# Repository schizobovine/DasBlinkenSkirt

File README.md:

# DasBlinkenSkirt
Firmware, hardware (?), and potentially sewing patterns for a RGB, motion-reactive, fiber-optic skirt (of a sort).

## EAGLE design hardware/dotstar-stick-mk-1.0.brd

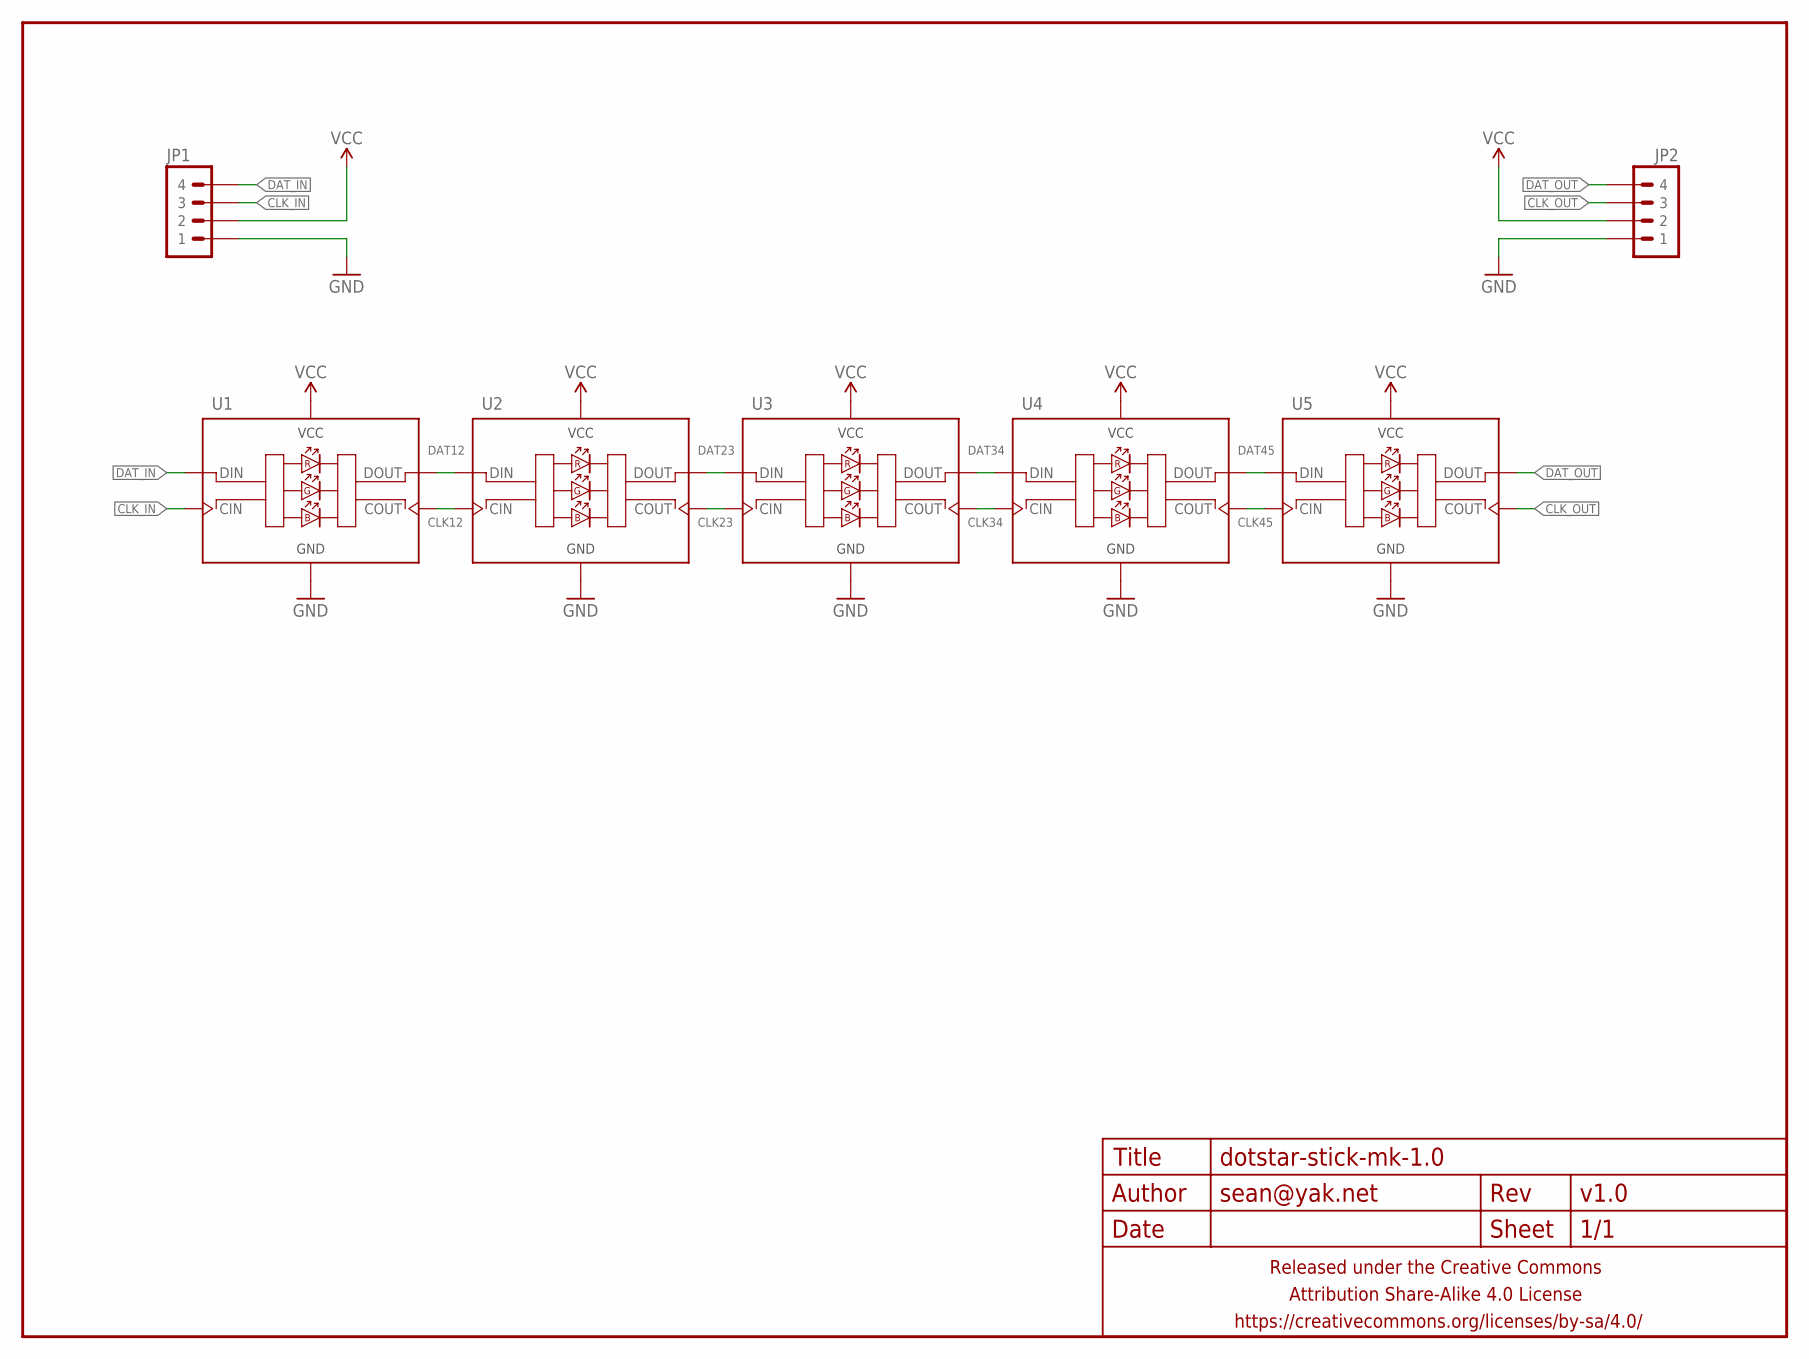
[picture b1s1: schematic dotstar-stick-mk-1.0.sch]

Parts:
FRAME1: FRAME-LETTERNO_PACKAGE; DUMMY
JP1, JP2: M04PTH-2MM-CENTERED; 1X04-2MM-CENTERED
U1, U2, U3, U4, U5: DOTSTARAPA102-5050; LED-5050

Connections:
CLK12: U1.5 (COUT), U2.2 (CIN)
CLK23: U2.5 (COUT), U3.2 (CIN)
CLK34: U3.5 (COUT), U4.2 (CIN)
CLK45: U4.5 (COUT), U5.2 (CIN)
CLK_IN: JP1.3, U1.2 (CIN)
CLK_OUT: JP2.3, U5.5 (COUT)
DAT12: U1.6 (DOUT), U2.1 (DIN)
DAT23: U2.6 (DOUT), U3.1 (DIN)
DAT34: U3.6 (DOUT), U4.1 (DIN)
DAT45: U4.6 (DOUT), U5.1 (DIN)
DAT_IN: JP1.4, U1.1 (DIN)
DAT_OUT: JP2.4, U5.6 (DOUT)
GND: JP1.1, JP2.1, U1.3 (GND), U2.3 (GND), U3.3 (GND), U4.3 (GND), U5.3 (GND)
VCC: JP1.2, JP2.2, U1.4 (VCC), U2.4 (VCC), U3.4 (VCC), U4.4 (VCC), U5.4 (VCC)

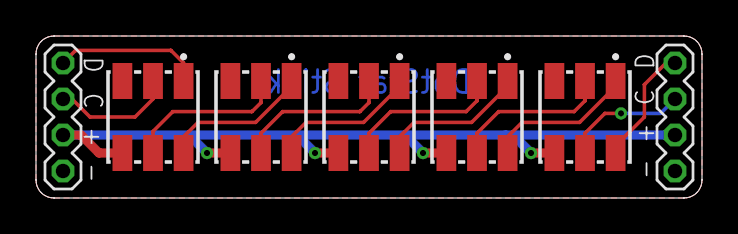
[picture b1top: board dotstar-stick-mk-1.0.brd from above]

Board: 2 copper layers, 37.0 x 9.0 mm, 8 parts (0 on the bottom side), 14 nets.

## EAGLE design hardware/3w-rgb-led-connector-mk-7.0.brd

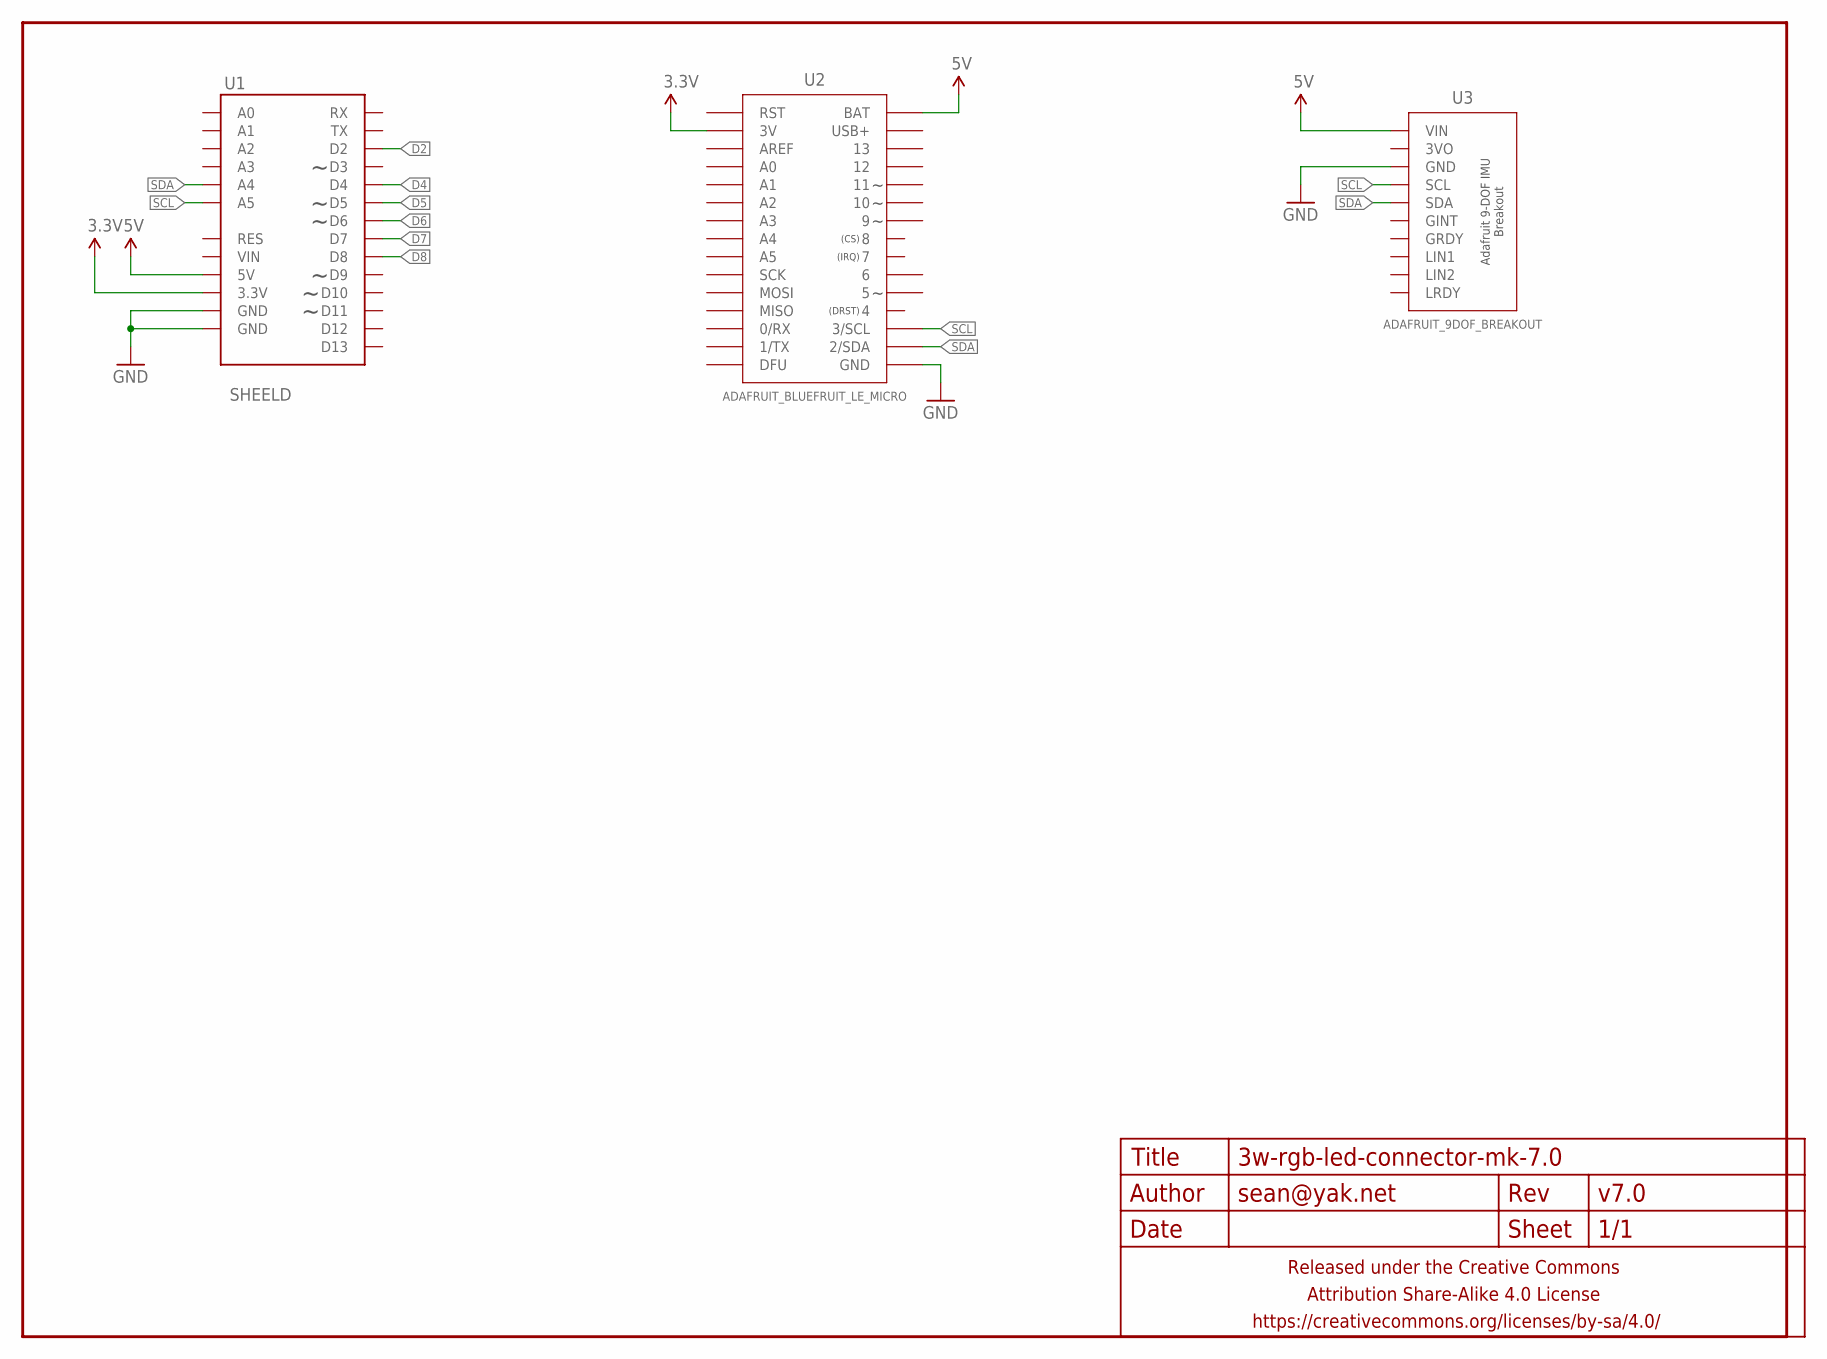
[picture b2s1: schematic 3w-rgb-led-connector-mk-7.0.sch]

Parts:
FRAME1: FRAME-LETTERNO_PACKAGE; DUMMY
U1: SHEELD; ARDUINO_SHIELD_NOOUTLINE_INSIDE_SMALLER
U2: ADAFRUIT_BLUEFRUIT_LE_MICRO
U3: ADAFRUIT_9DOF_BREAKOUT

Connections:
3.3V: U1.3.3V, U2.3V3 (3V)
5V: U1.5V, U2.BAT, U3.VIN
D2: U1.D2
D4: U1.D4
D5: U1.D5
D6: U1.D6
D7: U1.D7
D8: U1.D8
GND: U1.GND@0 (GND), U1.GND@1 (GND), U2.GND@1 (GND), U2.GND@2 (GND), U2.GND@3 (GND), U3.GND
SCL: U1.A5, U2.3/SCL, U3.SCL
SDA: U1.A4, U2.2/SDA, U3.SDA

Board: 2 copper layers, 4 parts (0 on the bottom side), 5 nets, no tracks yet.

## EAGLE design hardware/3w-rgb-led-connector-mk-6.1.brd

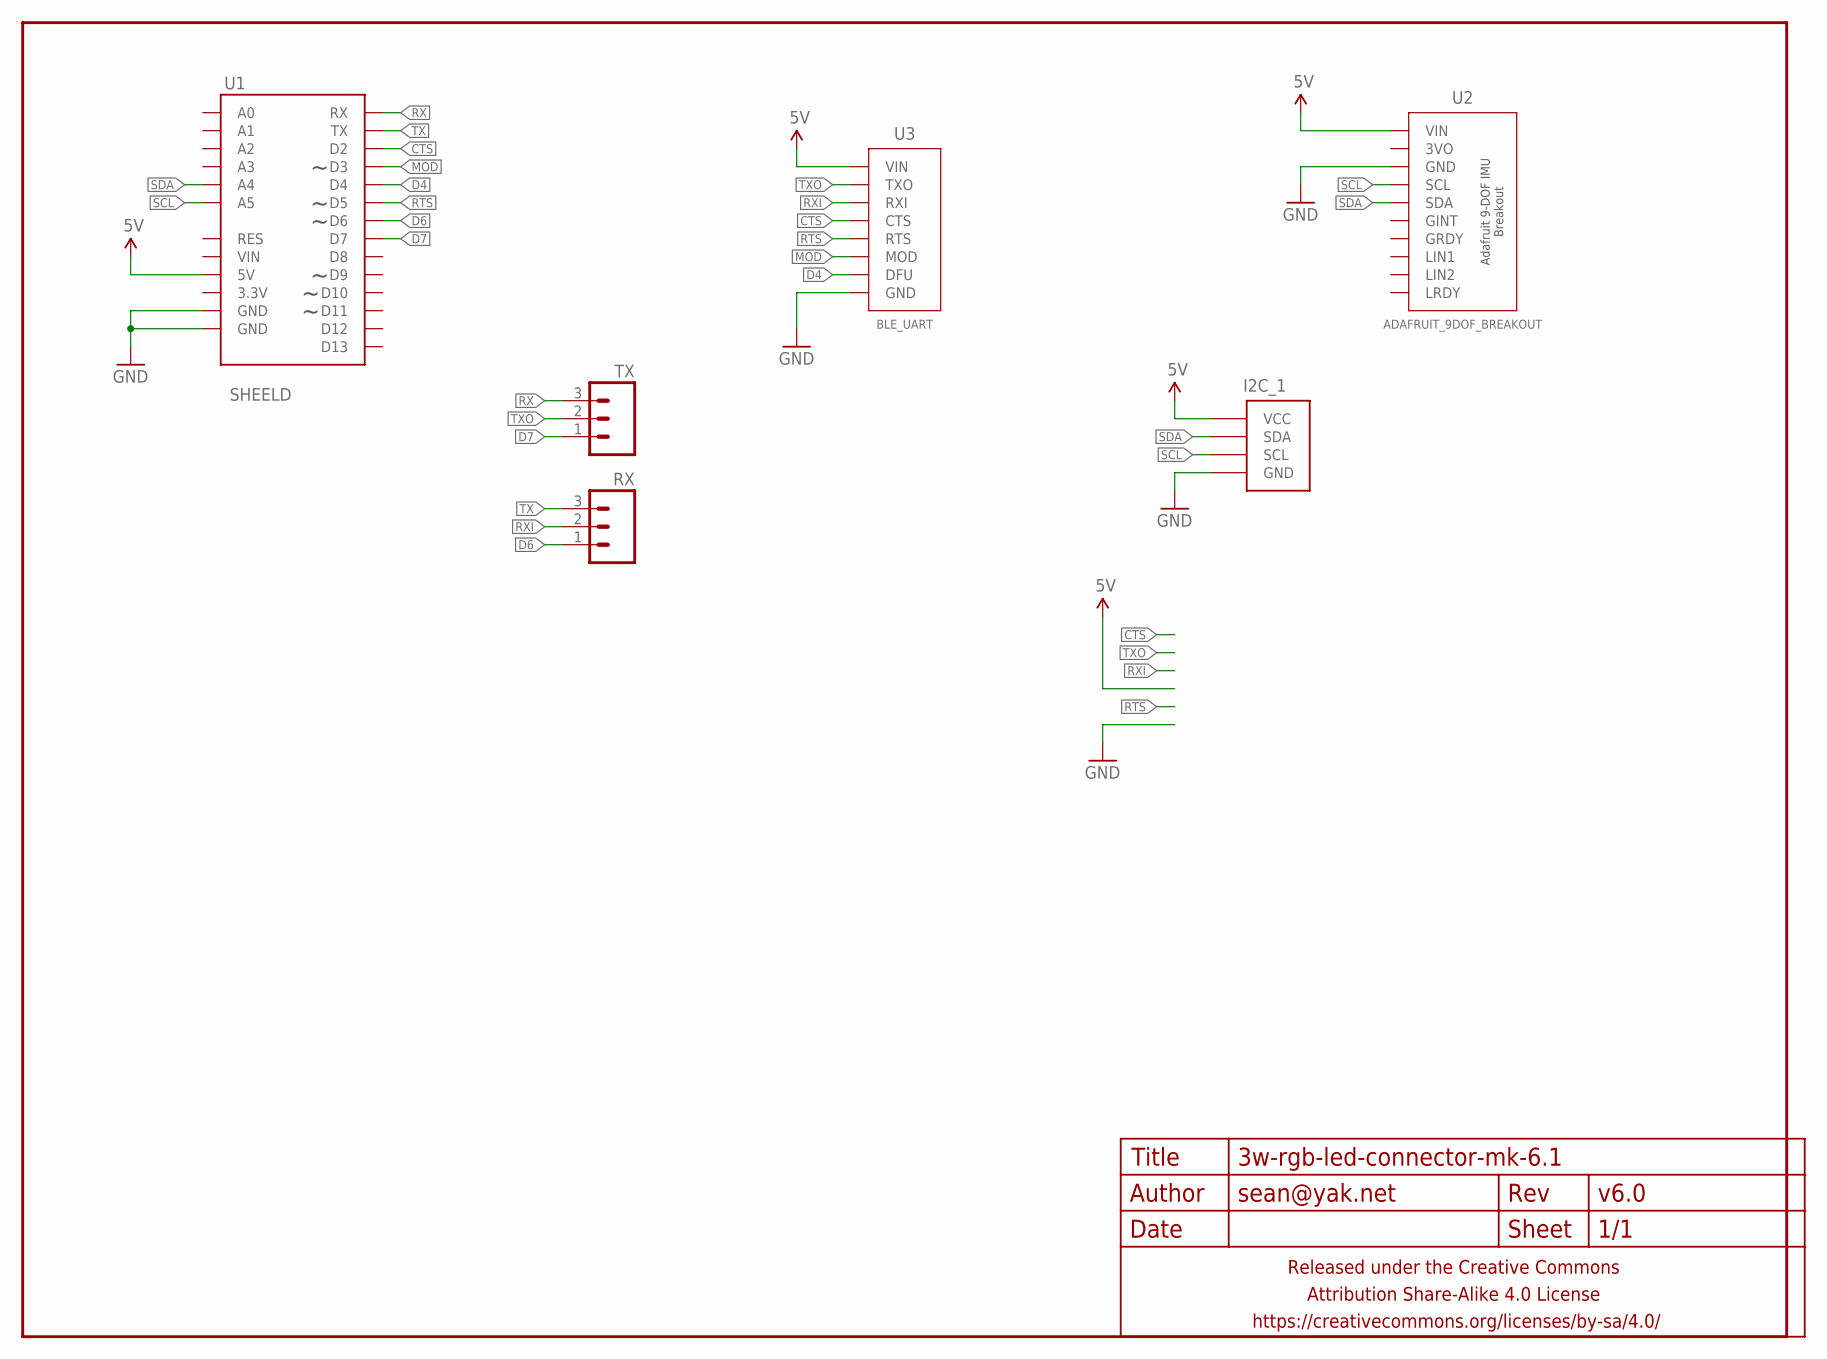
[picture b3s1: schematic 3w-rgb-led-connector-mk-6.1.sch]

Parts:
FRAME1: FRAME-LETTERNO_PACKAGE; DUMMY
I2C_1: M04-I2CPTH-0.1IN; 1X04-PTH-VERT-I2C
RX: M03PTH-CENTERED; 1X03-CENTERED
TX: M03PTH-CENTERED; 1X03-CENTERED
U1: SHEELD; ARDUINO_SHIELD_NOOUTLINE_INSIDE_SMALLER
U2: ADAFRUIT_9DOF_BREAKOUT
U3: BLE_UART; ADAFRUIT_BLE_UART_NOTHOLEY

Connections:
5V: I2C_1.VCC, U1.5V, U2.VIN, U3.VIN
CTS: U1.D2, U3.CTS
D4: U1.D4, U3.DFU
D6: RX.1, U1.D6
D7: TX.1, U1.D7
GND: I2C_1.GND, U1.GND@0 (GND), U1.GND@1 (GND), U2.GND, U3.GND
MOD: U1.D3, U3.MOD
RTS: U1.D5, U3.RTS
RX: TX.3, U1.RX
RXI: RX.2, U3.RXI
SCL: I2C_1.SCL, U1.A5, U2.SCL
SDA: I2C_1.SDA, U1.A4, U2.SDA
TX: RX.3, U1.TX
TXO: TX.2, U3.TXO

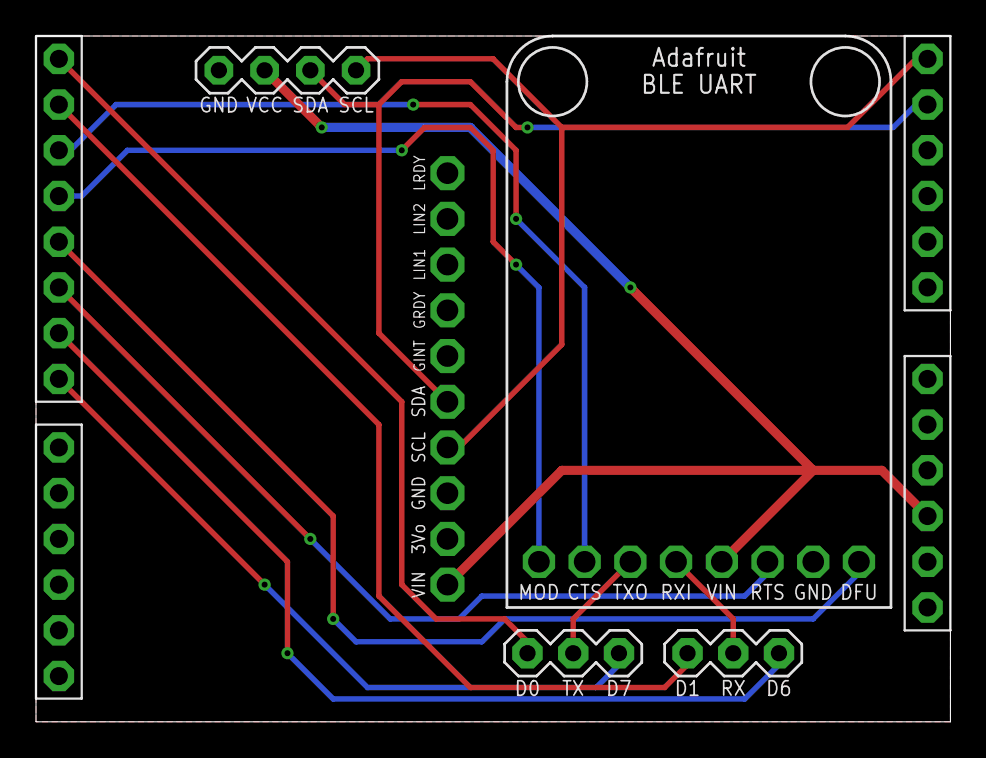
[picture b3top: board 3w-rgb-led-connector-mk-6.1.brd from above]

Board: 2 copper layers, 50.8 x 38.1 mm, 7 parts (0 on the bottom side), 14 nets.

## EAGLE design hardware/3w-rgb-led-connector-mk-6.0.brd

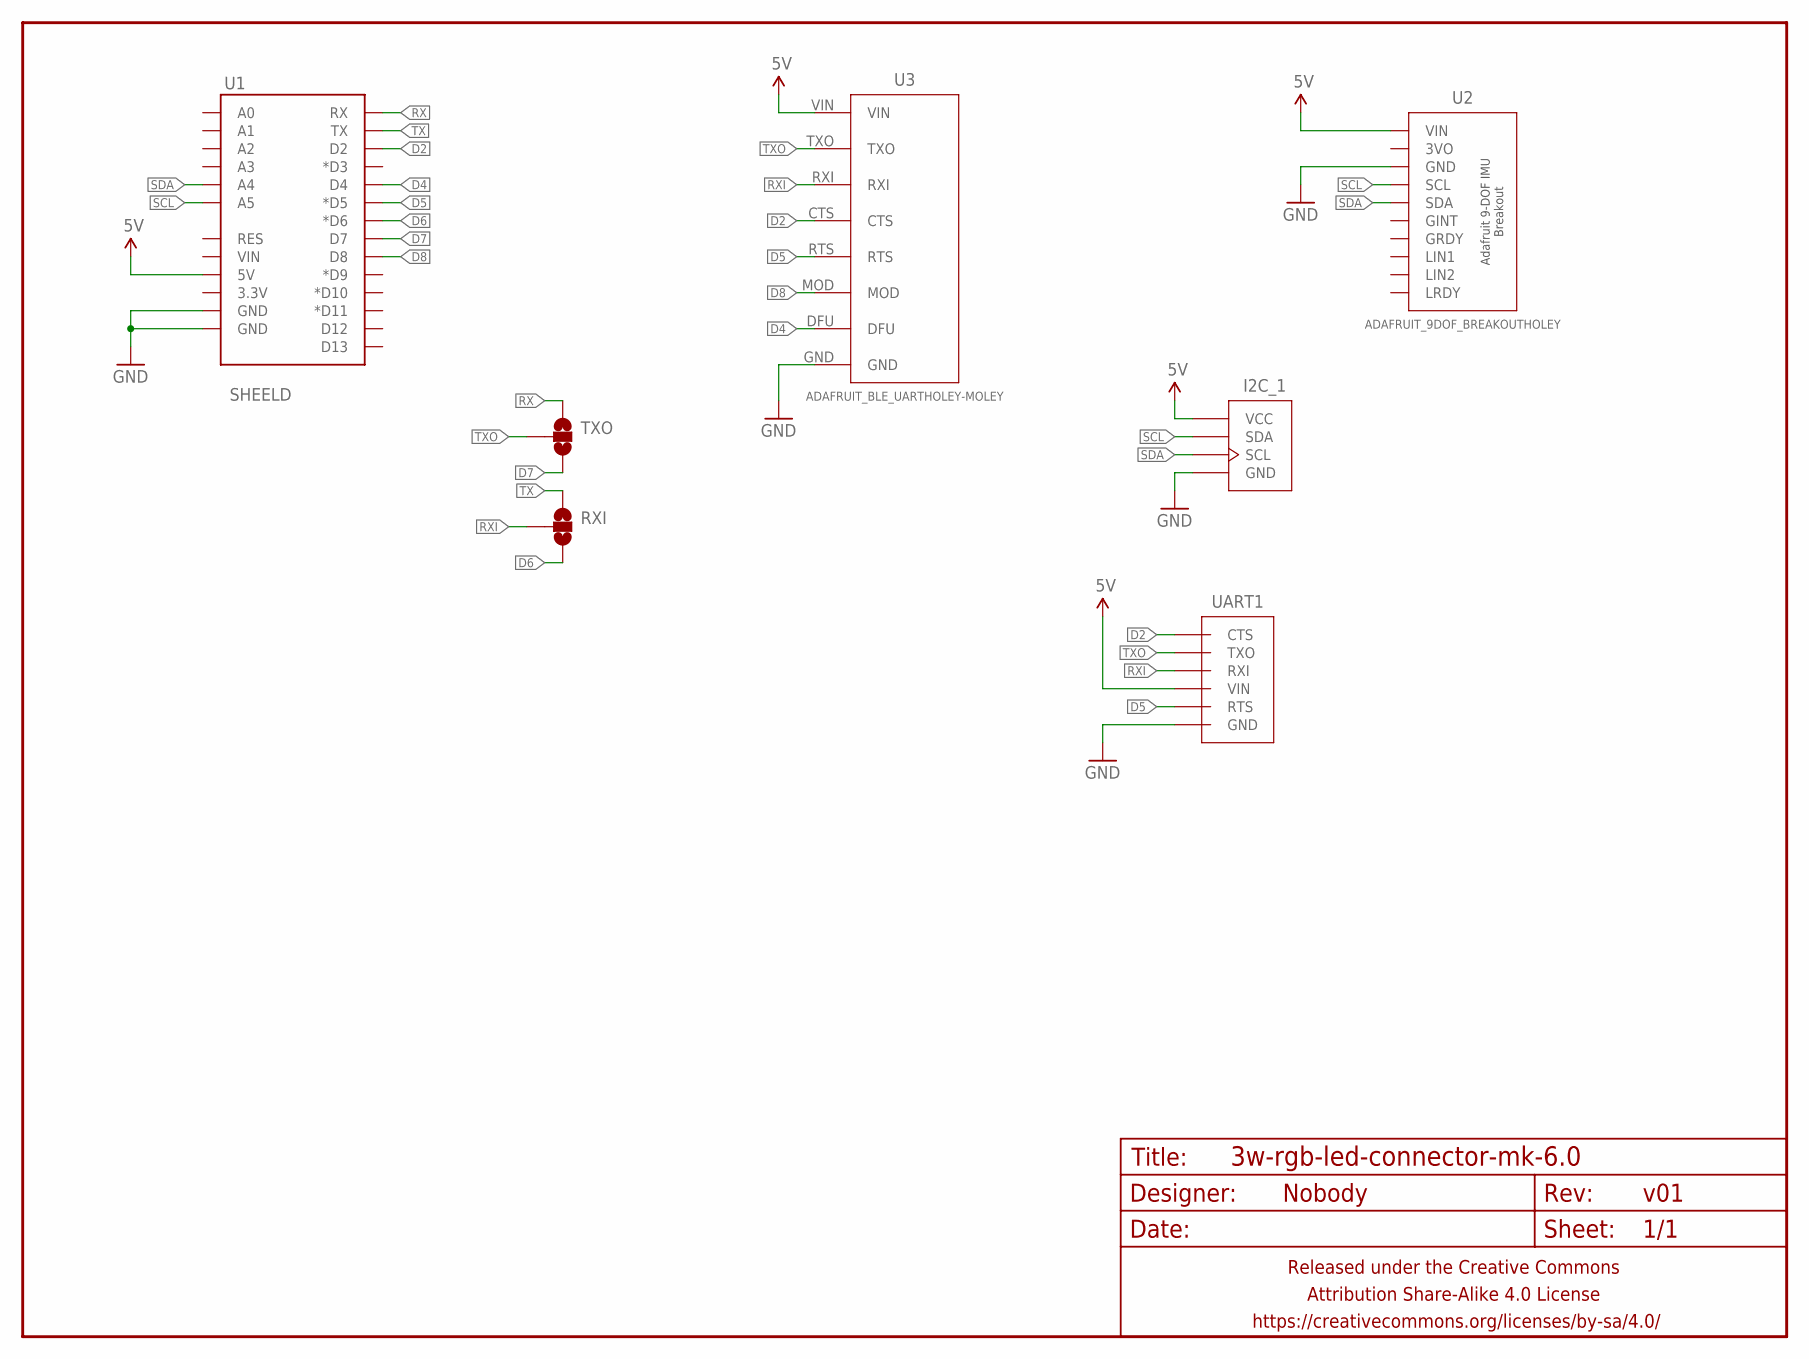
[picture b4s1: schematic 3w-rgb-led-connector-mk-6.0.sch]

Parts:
FRAME1: FRAME-LETTERNO_PACKAGE; DUMMY
I2C_1: M04-I2CPTH-0.1IN; 1X04-PTH-VERT-I2C
RXI: JUMPER-PAD-3-NOFULL_BOX_SILK; PAD-JUMPER-3-NO_YES_SILK_FULL_BOX
TXO: JUMPER-PAD-3-NOFULL_BOX_SILK; PAD-JUMPER-3-NO_YES_SILK_FULL_BOX
U1: SHEELD; ARDUINO_SHIELD_NOOUTLINE_INSIDE_SMALLER
U2: ADAFRUIT_9DOF_BREAKOUTHOLEY; ADAFRUIT_9DOF_BREAKOUT_HOLEY
U3: ADAFRUIT_BLE_UARTHOLEY-MOLEY; ADAFRUIT_BLE_UART_HOLEY
UART1: M06-UARTPTH-0.1IN; 1X06_PTH_UART

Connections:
5V: I2C_1.VCC, U1.5V, U2.VIN, U3.VIN, UART1.VCC (VIN)
D2: U1.D2, U3.CTS, UART1.CTS
D4: U1.D4, U3.DFU
D5: U1.D5 (*D5), U3.RTS, UART1.RTS
D6: RXI.3, U1.D6 (*D6)
D7: TXO.3, U1.D7
D8: U1.D8, U3.MOD
GND: I2C_1.GND, U1.GND@0 (GND), U1.GND@1 (GND), U2.GND, U3.GND, UART1.GND
RX: TXO.1, U1.RX
RXI: RXI.2, U3.RXI, UART1.RXI
SCL: I2C_1.SDA, U1.A5, U2.SCL
SDA: I2C_1.SCL, U1.A4, U2.SDA
TX: RXI.1, U1.TX
TXO: TXO.2, U3.TXO, UART1.TXO

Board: 2 copper layers, 8 parts (3 on the bottom side), 14 nets, no tracks yet.

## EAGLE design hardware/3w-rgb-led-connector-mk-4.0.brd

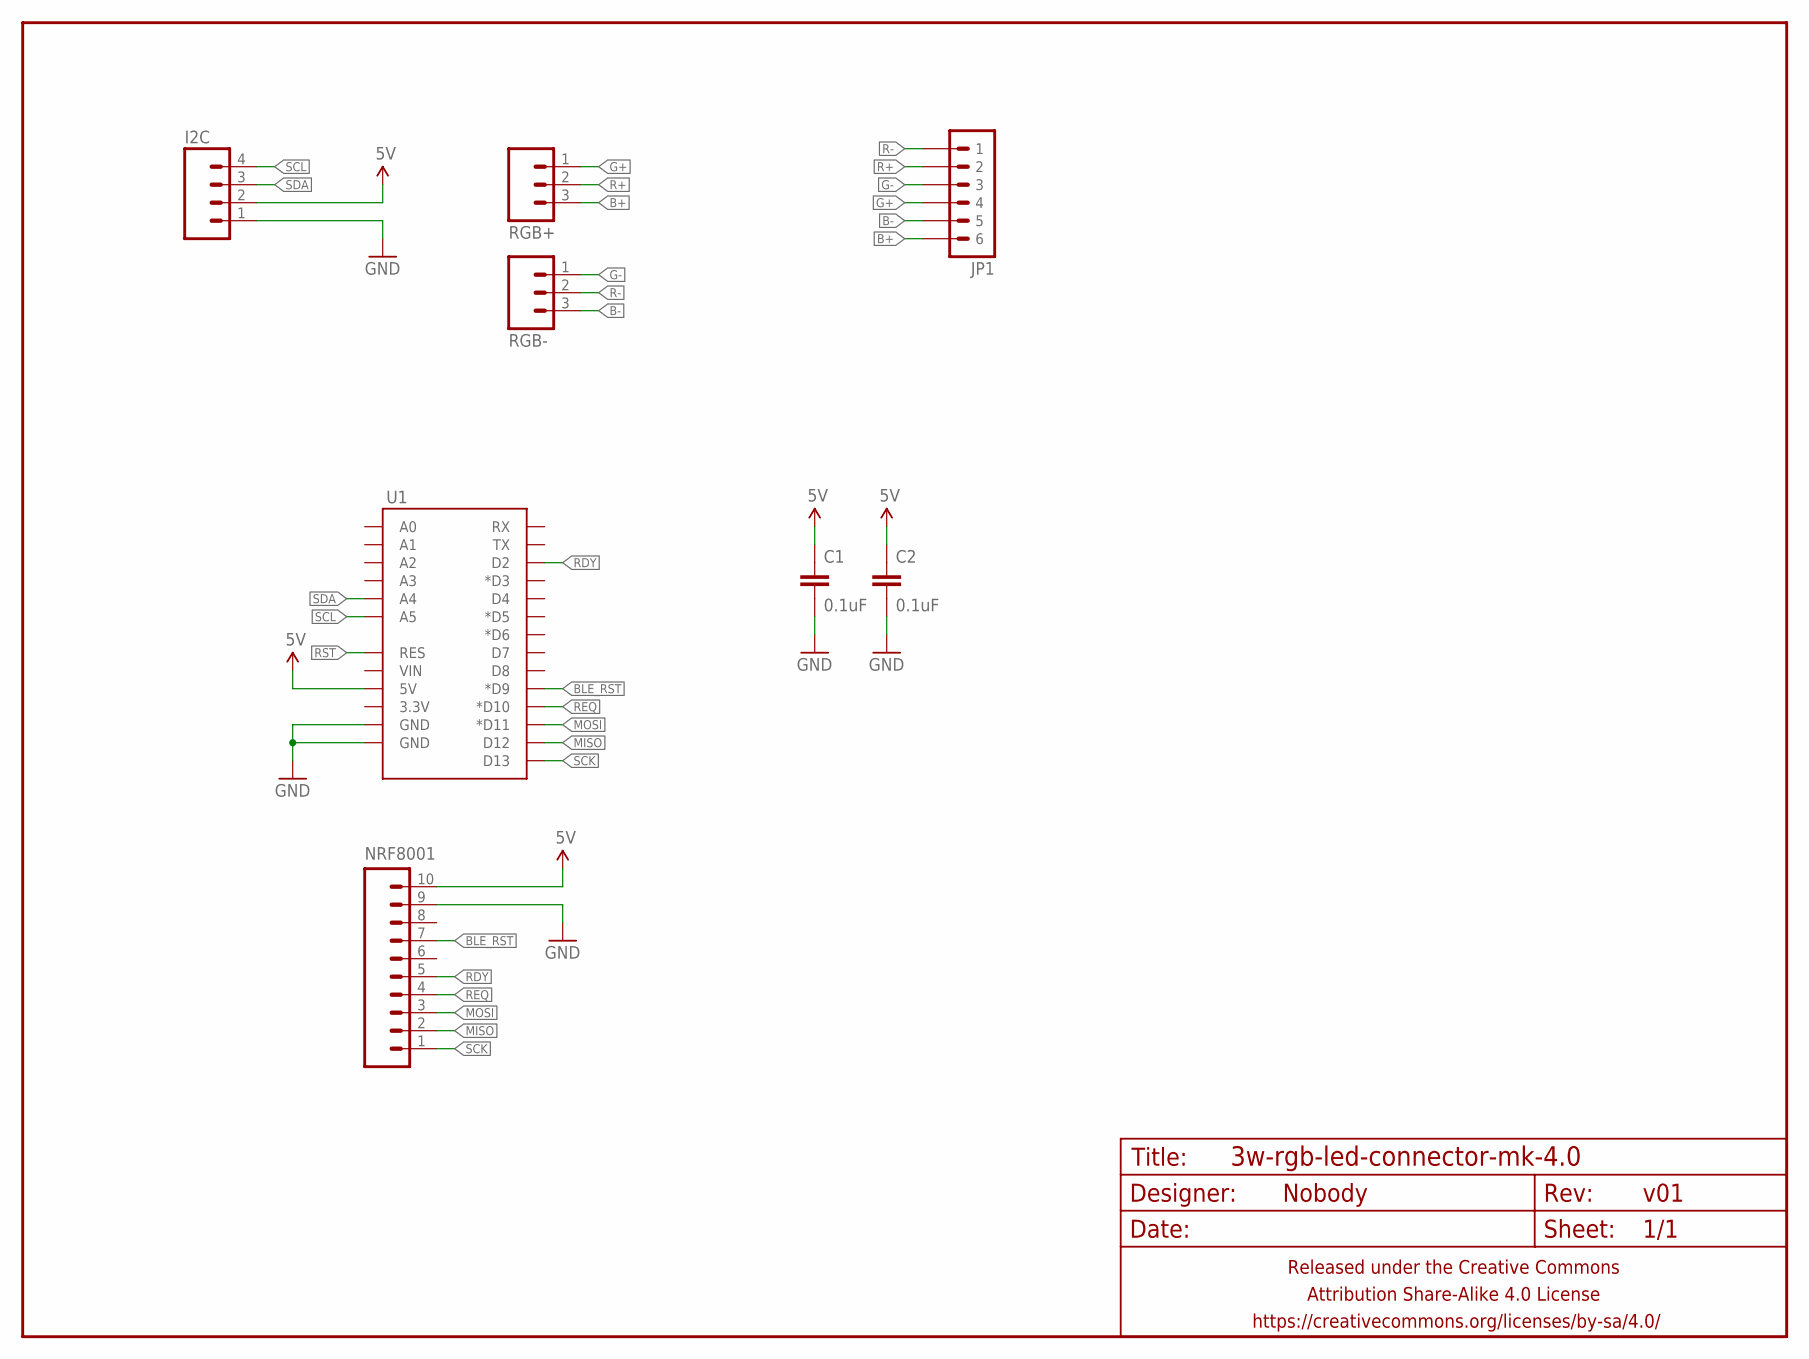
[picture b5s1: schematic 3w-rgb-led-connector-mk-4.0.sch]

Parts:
C1, C2: 0.1uF; C025-024X044
FRAME1: FRAME-LETTERNO_PACKAGE; DUMMY
I2C: M04JST_XH_RA; JST-4-XH-RA-PTH
JP1: M06JST-XH-RA-PTH-LONG; 1X06-2.5MM-JST-XH-RA-LONG
NRF8001: M10PTH-SLIM-ASS; 1X10_PTH_SLIMASS
RGB+: M03JST-3-XH-RA-PTH-LONG; JST-3-XH-RA-PTH-LONG
RGB-: M03JST-3-XH-RA-PTH-LONG; JST-3-XH-RA-PTH-LONG
U1: ARDUINO_SHIELD_SMALLER; ARDUINO_SHIELD_NOOUTLINE_INSIDE_SMALLER

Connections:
5V: C1.1, C2.1, I2C.2, NRF8001.10, U1.5V
B+: JP1.6, RGB+.3
B-: JP1.5, RGB-.3
BLE_RST: NRF8001.7, U1.D9 (*D9)
G+: JP1.4, RGB+.1
G-: JP1.3, RGB-.1
GND: C1.2, C2.2, I2C.1, NRF8001.9, U1.GND@0 (GND), U1.GND@1 (GND)
MISO: NRF8001.2, U1.D12
MOSI: NRF8001.3, U1.D11 (*D11)
R+: JP1.2, RGB+.2
R-: JP1.1, RGB-.2
RDY: NRF8001.5, U1.D2
REQ: NRF8001.4, U1.D10 (*D10)
RST: U1.RES
SCK: NRF8001.1, U1.D13
SCL: I2C.4, U1.A5
SDA: I2C.3, U1.A4

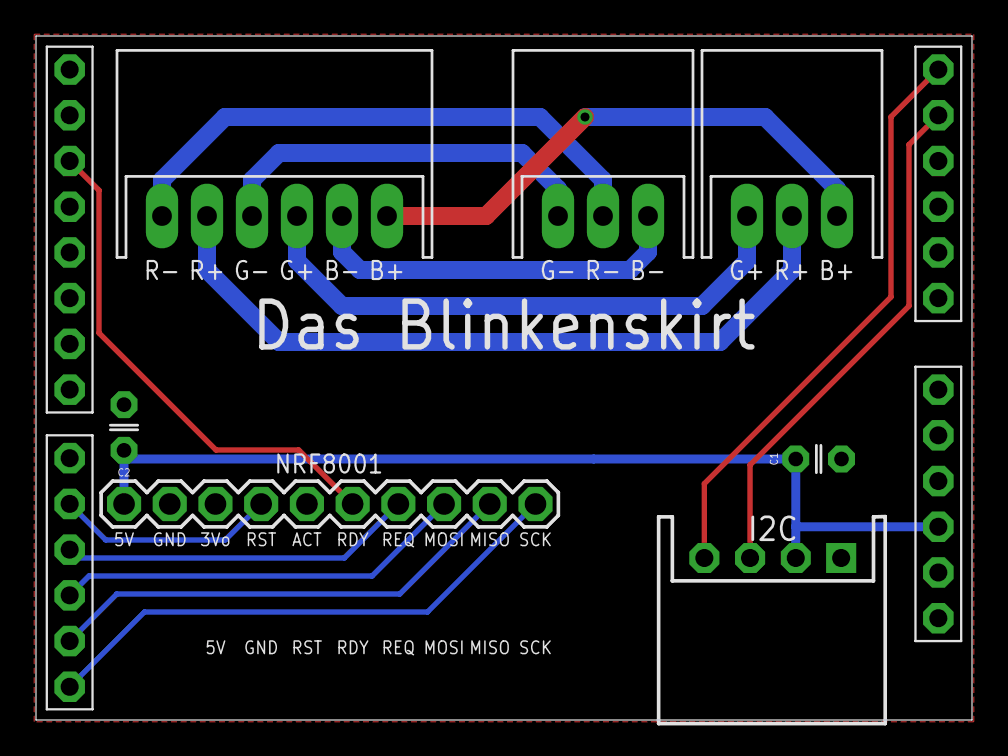
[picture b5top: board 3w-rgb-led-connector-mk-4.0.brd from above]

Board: 2 copper layers, 52.0 x 38.0 mm, 9 parts (0 on the bottom side), 16 nets.

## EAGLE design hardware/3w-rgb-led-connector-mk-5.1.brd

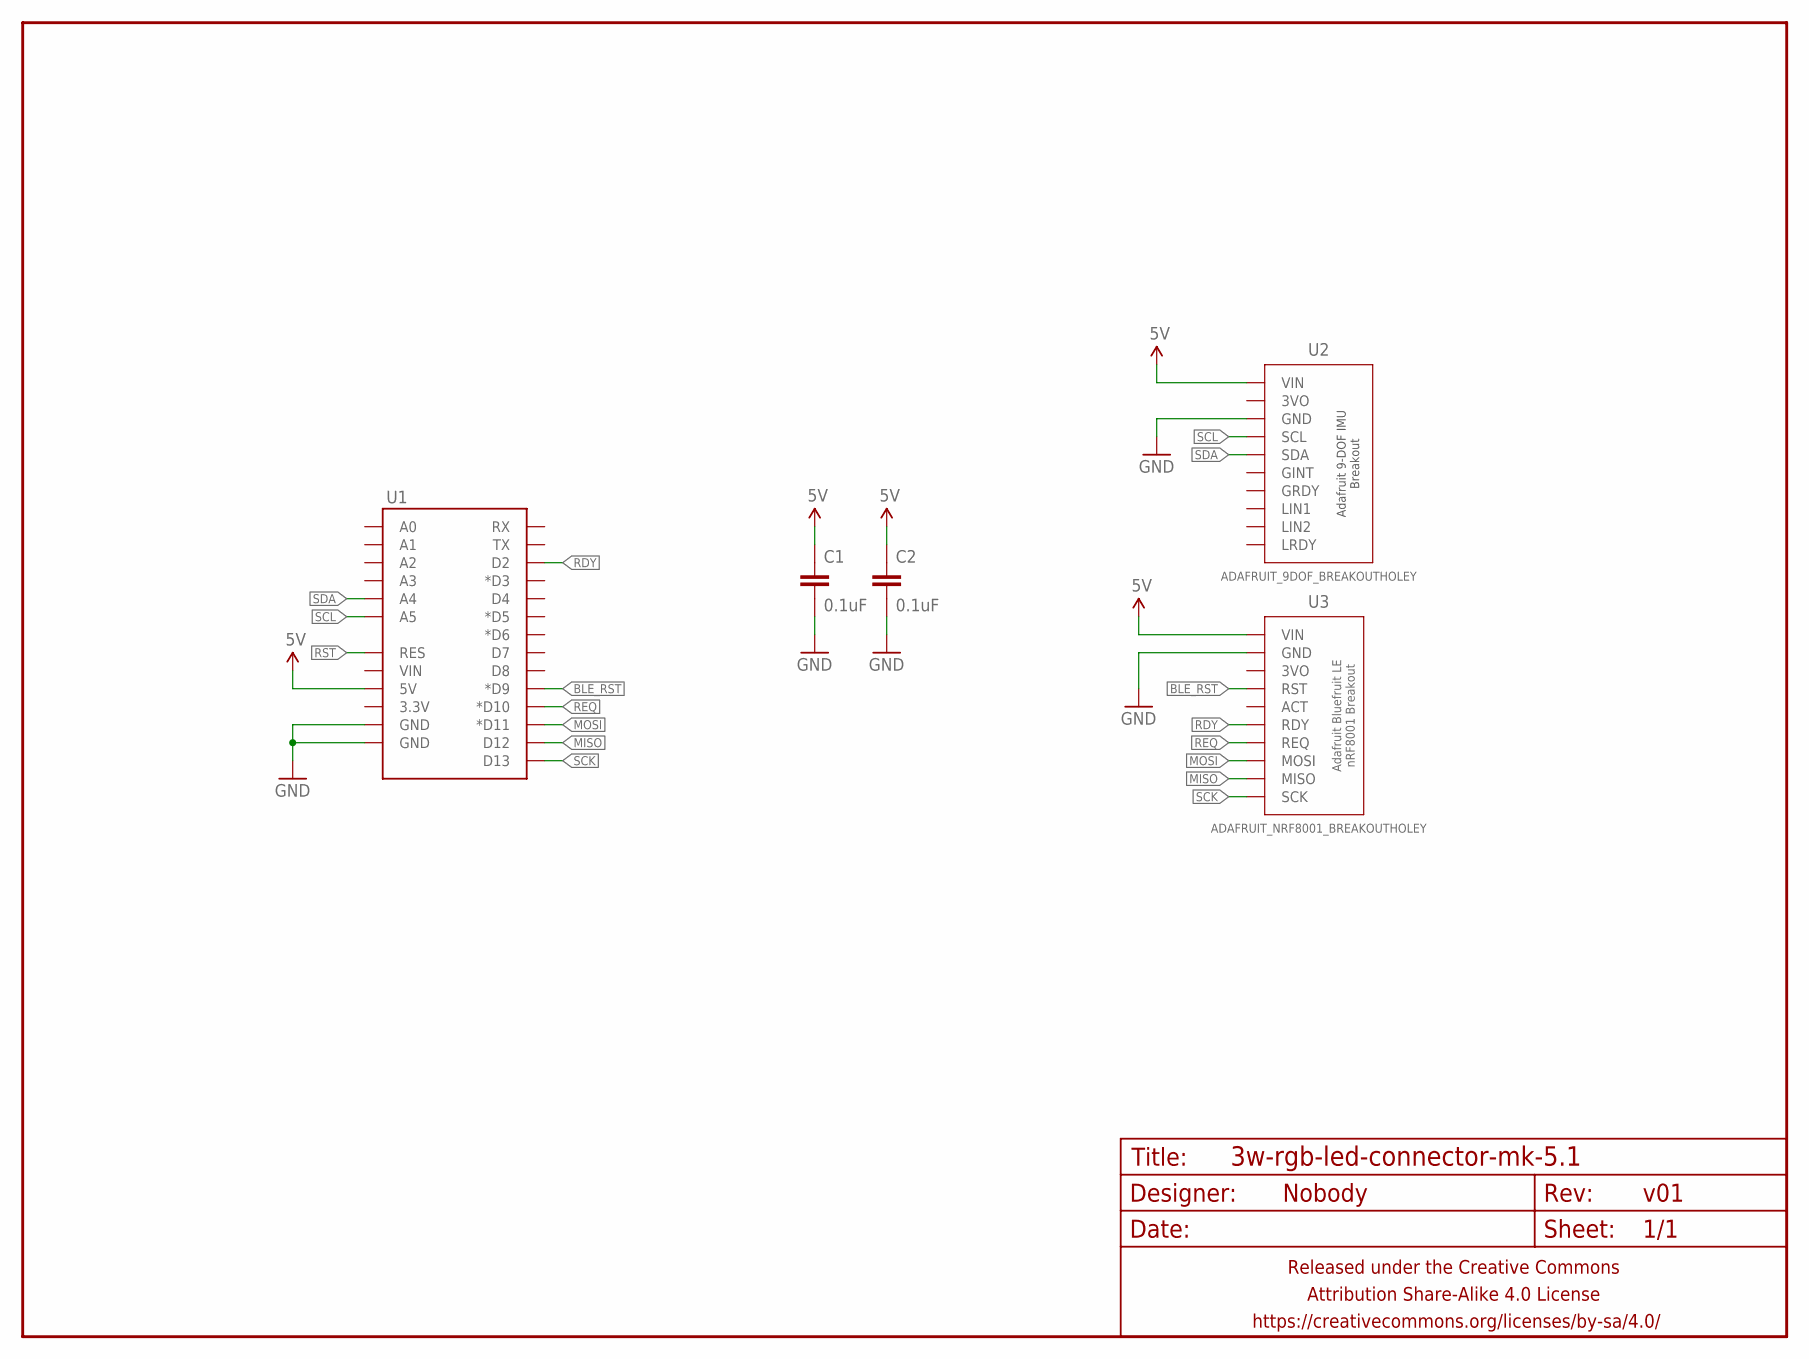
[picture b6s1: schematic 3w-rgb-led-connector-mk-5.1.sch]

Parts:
C1, C2: 0.1uF; C025-024X044
FRAME1: FRAME-LETTERNO_PACKAGE; DUMMY
U1: ARDUINO_SHIELD_SMALLER; ARDUINO_SHIELD_NOOUTLINE_INSIDE_SMALLER
U2: ADAFRUIT_9DOF_BREAKOUTHOLEY; ADAFRUIT_9DOF_BREAKOUT_HOLEY
U3: ADAFRUIT_NRF8001_BREAKOUTHOLEY; ADAFRUIT_NRF8001_HOLEY

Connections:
5V: C1.1, C2.1, U1.5V, U2.VIN, U3.VIN
BLE_RST: U1.D9 (*D9), U3.RST
GND: C1.2, C2.2, U1.GND@0 (GND), U1.GND@1 (GND), U2.GND, U3.GND
MISO: U1.D12, U3.MISO
MOSI: U1.D11 (*D11), U3.MOSI
RDY: U1.D2, U3.RDY
REQ: U1.D10 (*D10), U3.REQ
RST: U1.RES
SCK: U1.D13, U3.SCK
SCL: U1.A5, U2.SCL
SDA: U1.A4, U2.SDA

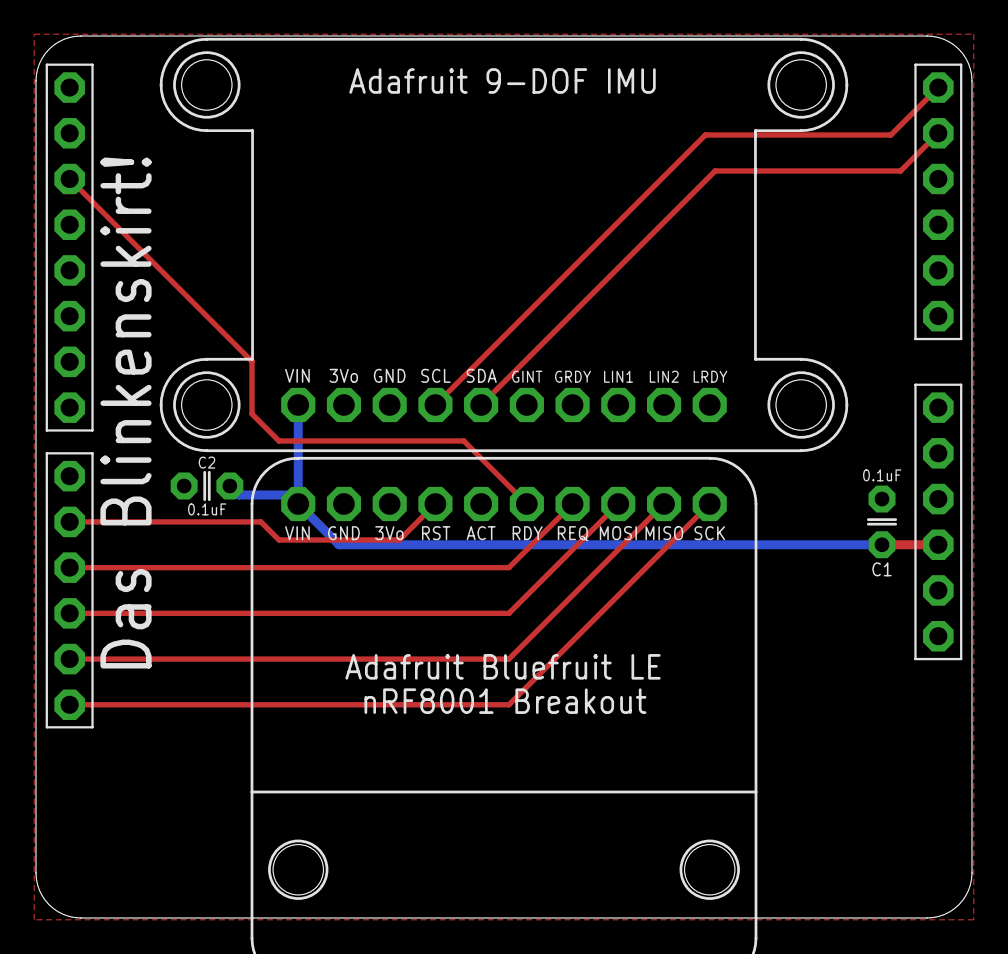
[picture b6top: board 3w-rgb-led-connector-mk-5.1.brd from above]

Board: 2 copper layers, 52.0 x 49.0 mm, 6 parts (0 on the bottom side), 10 nets.

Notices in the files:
parts and their libraries:
A_butts: Released under the Creative Commons Attribution Share-Alike 4.0 License
A_butts: https://creativecommons.org/licenses/by-sa/4.0
A_butts: Released under the Creative Commons
